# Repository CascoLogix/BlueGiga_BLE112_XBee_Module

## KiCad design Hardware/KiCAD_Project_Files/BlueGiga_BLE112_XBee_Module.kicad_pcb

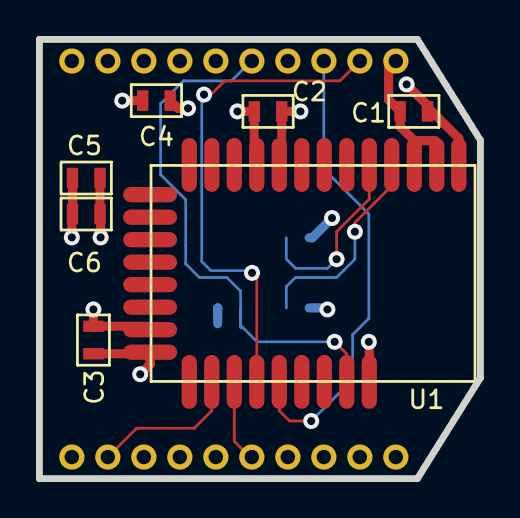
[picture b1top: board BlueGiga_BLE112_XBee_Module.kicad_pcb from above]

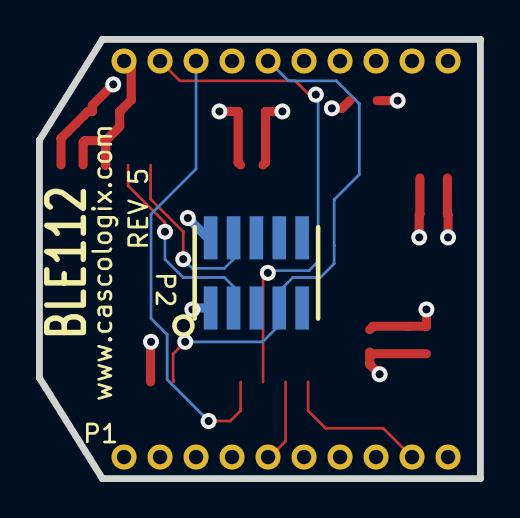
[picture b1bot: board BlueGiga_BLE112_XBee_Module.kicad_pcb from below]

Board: 4 copper layers, 24.5 x 24.4 mm, 9 parts (2 on the bottom side), 9 nets.

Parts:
C1, C2, C3: 1u; C0603
C4, C5: 4.7u; C0603
C6: 0.47u; C0603
P1: XBEE HEADER; HEADER_XBEE
P2: DEBUG; HEADER_50MIL_2R10P_SMT
U1: BLE112-A; BLE112

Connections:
+3V3: C1.1, C2.1, C3.1, C4.1, C5.1, C6.1, P1.1, P2.2, U1.2, U1.3, U1.9, U1.20
CT: P1.16, U1.24
GND: C1.2, C2.2, C3.2, C4.2, C5.2, C6.2, P1.10, P2.1, U1.1, U1.10, U1.21, U1.30
P2_1: P2.4, U1.5
P2_2: P2.3, U1.4
RESET: P1.5, P2.7, U1.29
RT: P1.12, U1.23
RX: P1.3, U1.26
TX: P1.2, U1.25

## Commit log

2013-11-11 Updated Schematic to add debug header and remove unused pin headers. PCB needs a few routes still and clean up debug header area.
2013-11-12 Rotated debug header 180 deg for better routing. Added dimensions to PCB. Board is 100% routed with good DRC. Need to generate gerbers and visually check each layer.
2013-11-14 Updated PCB layout to put 2mm pin header at same location as the RN-41XV. Added silkscreen artwork to back of PCB. Added assembly pdf drawings and schematic pdf. Added OSH Park PCB render images.
2014-11-28 Fixed debugger connector, added renders, updated board drawings with layout changes and rev and date.
2014-11-28 Removed .hgignore file
2015-04-25 Corrected voltage regulator connections and added level shifters to inputs to BLE112.
2015-04-25 Corrected OSH Park gerber archive (missing internal plane layers).
2015-05-02 Simplified design into a 3.3V-only. A branch has been started to continue to support potential dual voltage (3.3V & 5V) designs.
2015-05-02 Corrected BOM per new 3.3V only design
2015-06-29 Correct BOM line numbering. Also removed 'special' library from project to stop the warning that it couldn't find the library.
2015-07-10 Updated product images
2015-07-14 Removed redundant or NVA images.
2015-07-16 Fixed layout/gerber issue shorting the power and ground plane together through two vias that did not have their clearance refreshed after the copper pour was filled.
2015-07-16 Corrected debug header connections where pin 9 was connected to 3.3V.
2015-07-29 Updated XBee Dubugger Connection image
